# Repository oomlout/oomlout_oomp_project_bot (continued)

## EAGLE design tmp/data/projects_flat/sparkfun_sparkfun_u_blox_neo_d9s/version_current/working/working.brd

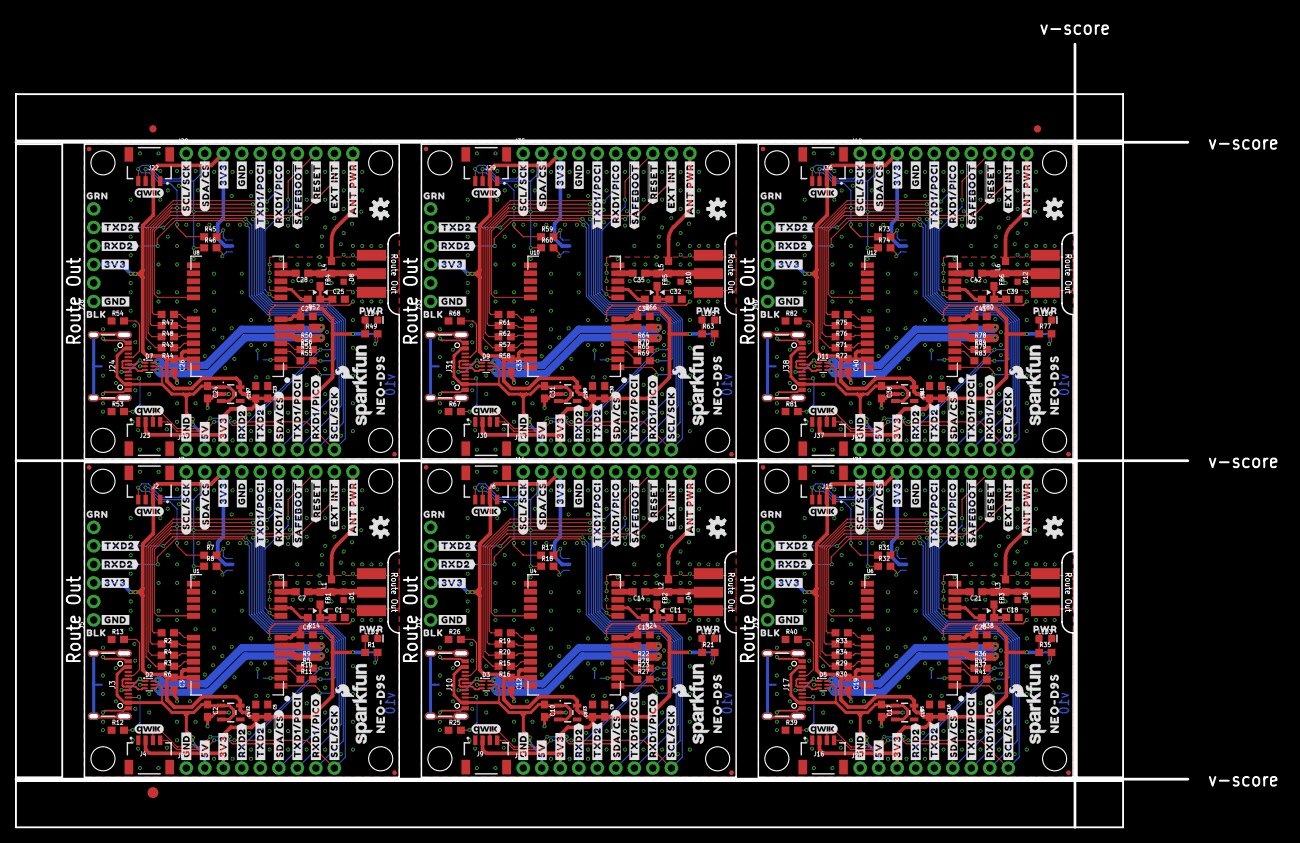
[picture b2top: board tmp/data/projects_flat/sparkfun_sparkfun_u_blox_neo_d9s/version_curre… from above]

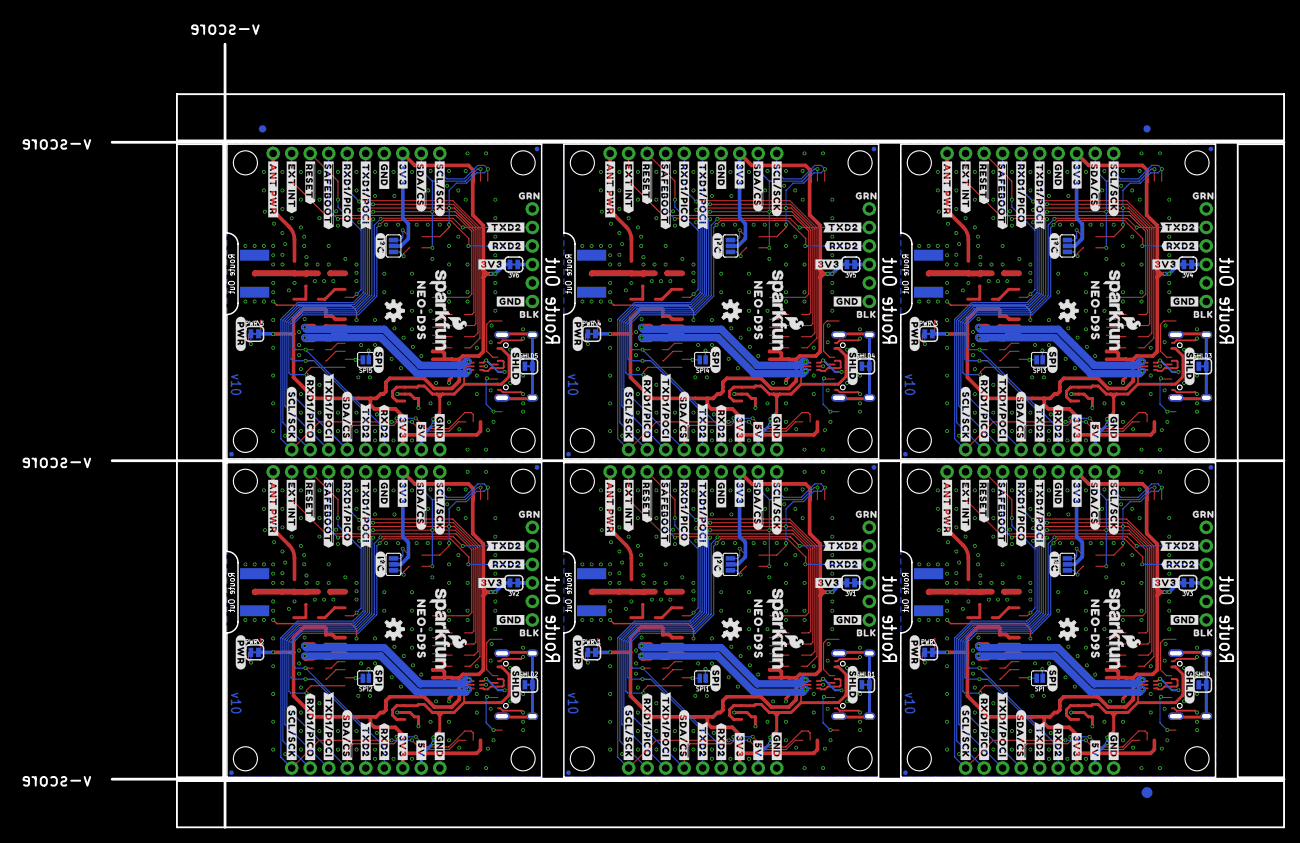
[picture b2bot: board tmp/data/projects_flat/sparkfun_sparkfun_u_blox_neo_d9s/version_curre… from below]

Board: 2 copper layers, 160.8 x 107.4 mm, 672 parts (237 on the bottom side), 228 nets.

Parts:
3V1, 3V2, 3V3, 3V4, 3V5, 3V6: JUMPER-SMT_2_NC_TRACE_SILK; SMT-JUMPER_2_NC_TRACE_SILK
C1, C7, C11, C14, C18, C21, C25, C28, C32, C35, C39, C42: 47pF; 0603
C2, C3, C4, C6, C8, C10, C12, C13, C15, C17, C19, C20, C22, C24, C26, C27, C29, C31, C33, C34, C36, C38, C40, C41: 1.0uF; 0603
C5, C9, C16, C23, C30, C37: 0.1uF; 0603
D1, D4, D6, D8, D10, D12: PESD0402-0402; 0402
D2, D3, D5, D7, D9, D11: PRTR5V0U2F; SOT886
E$1, E$2, E$3, E$4: FIDUCIAL-1X2
E$5, E$6: FIDUCIAL-1.5X3
FB1, FB2, FB3, FB4, FB5, FB6: 30Ω/1.8A; 0603
I2C, I2C1, I2C2, I2C3, I2C4, I2C5: JUMPER-SMT_3_NO_SILK; SMT-JUMPER_3_NO_SILK
J1, J11, J18, J25, J32, J39: ANTENNA-SMA-GROUNDEDEDGE_SMA; SMA-EDGE
J2, J4, J6, J9, J15, J16, J22, J23, J29, J30, J36, J37: Qwiic Right Angle; JST04_1MM_RA
J3, J10, J17, J24, J31, J38: USB-C-16P-2LAYER-PADS
J5, J12, J19, J26, J33, J40: 1X06_NO_SILK
J7, J14, J21, J28, J35, J42: 1X10_NO_SILK
J8, J13, J20, J27, J34, J41: 1X09_NO_SILK
JP1, JP2, JP7, JP8, JP9, JP10, JP15, JP16, JP17, JP18, JP24, JP25, JP26, JP27, JP31, JP33, JP34, JP35, JP36, JP41, JP42, JP43, JP91, JP101: STAND-OFF
JP3, JP4, JP5, JP6, JP11, JP12, JP13, JP14, JP19, JP20, JP21, JP22, JP23, JP28, JP29, JP30, JP32, JP37, JP38, JP39, JP40, JP61, JP71, JP81: FIDUCIALUFIDUCIAL; MICRO-FIDUCIAL
L1, L2, L3, L4, L5, L6: DNP; 0603_NO-CREAM
LED1, LED2, LED3, LED4, LED5, LED6: RED; LED-0603
LOGO1, LOGO4, LOGO5, LOGO8, LOGO9, LOGO12, LOGO13, LOGO16, LOGO17, LOGO20, LOGO21, LOGO24: OSHW-LOGOS; OSHW-LOGO-S
LOGO2, LOGO3, LOGO6, LOGO7, LOGO10, LOGO11, LOGO14, LOGO15, LOGO18, LOGO19, LOGO22, LOGO23: SFE_LOGO_NAME_FLAME.1_INCH; SFE_LOGO_NAME_FLAME_.1
PWR\, PWR\1, PWR\2, PWR\3, PWR\4, PWR\5: JUMPER-SMT_2_NC_TRACE_SILK; SMT-JUMPER_2_NC_TRACE_SILK
R1, R21, R35, R49, R63, R77: 1k; 0603
R2, R3, R4, R5, R6, R11, R15, R16, R19, R20, R27, R28, R29, R30, R33, R34, R41, R42, R43, R44, R47, R48, R55, R56, R57, R58, R61, R62, R69, R70, R71, R72, R75, R76, R83, R84: 33; 0603
R7, R8, R17, R18, R31, R32, R45, R46, R59, R60, R73, R74: 2.2k; 0603
R9, R10, R22, R23, R36, R37, R50, R51, R64, R65, R78, R79: 27; 0603
R12, R13, R25, R26, R39, R40, R53, R54, R67, R68, R81, R82: 5.1k; 0603
R14, R24, R38, R52, R66, R80: 10; 0603
SHLD, SHLD1, SHLD2, SHLD3, SHLD4, SHLD5: JUMPER-SMT_2_NC_TRACE_SILK; SMT-JUMPER_2_NC_TRACE_SILK
SPI, SPI1, SPI2, SPI3, SPI4, SPI5: JUMPER-SMT_2_NO_SILK; SMT-JUMPER_2_NO_SILK
U1, U4, U6, U8, U10, U12: U-BLOX_NEO-D9S-00B; NEO-M9N/M8T/M8U/D9S
U2, U3, U5, U7, U9, U11: 3.3V; SOT23-5
U$1, U$2, U$3, U$61, U$62, U$63, U$120, U$121, U$122, U$179, U$180, U$181, U$238, U$239, U$240, U$297, U$298, U$299: #GND#0
U$4, U$5, U$6, U$64, U$65, U$66, U$123, U$124, U$125, U$182, U$183, U$184, U$241, U$242, U$243, U$300, U$301, U$302: #GND#1
U$7, U$8, U$67, U$68, U$126, U$127, U$185, U$186, U$244, U$245, U$303, U$304: #TXD2#0
U$9, U$10, U$69, U$70, U$128, U$129, U$187, U$188, U$246, U$247, U$305, U$306: #TXD2#3
U$11, U$12, U$71, U$72, U$130, U$131, U$189, U$190, U$248, U$249, U$307, U$308: #RXD2#0
U$13, U$15, U$73, U$74, U$132, U$133, U$191, U$192, U$250, U$251, U$309, U$310: #RXD2#3
U$14, U$38, U$60, U$114, U$119, U$173, U$178, U$232, U$237, U$291, U$296, U$350: QWIIC_4MM
U$16, U$17, U$75, U$76, U$134, U$135, U$193, U$194, U$252, U$253, U$311, U$312: BLK0
U$18, U$19, U$77, U$78, U$136, U$137, U$195, U$196, U$254, U$255, U$313, U$314: GRN0
U$20, U$79, U$138, U$197, U$256, U$315: #5V#0
U$21, U$80, U$139, U$198, U$257, U$316: #5V#6
U$22, U$23, U$56, U$57, U$81, U$82, U$115, U$116, U$140, U$141, U$174, U$175, U$199, U$200, U$233, U$234, U$258, U$259, U$292, U$293, U$317, U$318, U$351, U$352: #3V3#0
U$24, U$25, U$83, U$84, U$142, U$143, U$201, U$202, U$260, U$261, U$319, U$320: #3V3#4
U$26, U$27, U$85, U$86, U$144, U$145, U$203, U$204, U$262, U$263, U$321, U$322: #SDA##CS##0
U$28, U$29, U$87, U$88, U$146, U$147, U$205, U$206, U$264, U$265, U$323, U$324: #SDA##CS##1
U$30, U$31, U$106, U$107, U$165, U$166, U$224, U$225, U$283, U$284, U$342, U$343: #TXD1#POCI#0
U$32, U$33, U$108, U$109, U$167, U$168, U$226, U$227, U$285, U$286, U$344, U$345: #TXD1#POCI#2
U$34, U$35, U$110, U$111, U$169, U$170, U$228, U$229, U$287, U$288, U$346, U$347: #RXD1#PICO#0
U$36, U$37, U$112, U$113, U$171, U$172, U$230, U$231, U$289, U$290, U$348, U$349: #RXD1#PICO#2
U$39, U$40, U$89, U$90, U$148, U$149, U$207, U$208, U$266, U$267, U$325, U$326: #SCL#SCK#0
U$41, U$42, U$91, U$92, U$150, U$151, U$209, U$210, U$268, U$269, U$327, U$328: #SCL#SCK#1
U$43, U$93, U$152, U$211, U$270, U$329: ##SAFEBOOT##0
U$44, U$94, U$153, U$212, U$271, U$330: ##SAFEBOOT##1
U$45, U$95, U$154, U$213, U$272, U$331: ##RESET##0
U$46, U$96, U$155, U$214, U$273, U$332: ##RESET##1
U$47, U$97, U$156, U$215, U$274, U$333: #EXT_INT#0
U$48, U$98, U$157, U$216, U$275, U$334: #EXT_INT#1
U$49, U$99, U$158, U$217, U$276, U$335: PWR0
U$50, U$100, U$159, U$218, U$277, U$336: #PWR#0
U$51, U$101, U$160, U$219, U$278, U$337: #SPI#0
U$52, U$102, U$161, U$220, U$279, U$338: #I�C#0
U$53, U$103, U$162, U$221, U$280, U$339: #SHLD#0
U$54, U$55, U$104, U$105, U$163, U$164, U$222, U$223, U$281, U$282, U$340, U$341: NEO#D9S0
U$58, U$117, U$176, U$235, U$294, U$353: #ANT_PWR#0
U$59, U$118, U$177, U$236, U$295, U$354: #ANT_PWR#1

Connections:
3.3V: 3V3.2, C3.1, C4.1, C5.2, C6.1, I2C.2, J2.2, J4.2, J7.3, J8.3, PWR\.2, U1.7, U1.22, U1.23, U2.5
3.3V1: 3V1.2, C8.1, C9.2, C12.1, C13.1, I2C1.2, J6.2, J9.2, J13.3, J14.3, PWR\1.2, U3.5, U4.7, U4.22, U4.23
3.3V2: 3V2.2, C15.1, C16.2, C19.1, C20.1, I2C2.2, J15.2, J16.2, J20.3, J21.3, PWR\2.2, U5.5, U6.7, U6.22, U6.23
3.3V3: 3V4.2, C22.1, C23.2, C26.1, C27.1, I2C3.2, J22.2, J23.2, J27.3, J28.3, PWR\3.2, U7.5, U8.7, U8.22, U8.23
3.3V4: 3V5.2, C29.1, C30.2, C33.1, C34.1, I2C4.2, J29.2, J30.2, J34.3, J35.3, PWR\4.2, U9.5, U10.7, U10.22, U10.23
3.3V5: 3V6.2, C36.1, C37.2, C40.1, C41.1, I2C5.2, J36.2, J37.2, J41.3, J42.3, PWR\5.2, U11.5, U12.7, U12.22, U12.23
5V: C2.1, D2.5, J3.VBUS1, J3.VBUS2, J8.2, U2.1, U2.3
5V1: C10.1, D3.5, J10.VBUS1, J10.VBUS2, J13.2, U3.1, U3.3
5V2: C17.1, D5.5, J17.VBUS1, J17.VBUS2, J20.2, U5.1, U5.3
5V3: C24.1, D7.5, J24.VBUS1, J24.VBUS2, J27.2, U7.1, U7.3
5V4: C31.1, D9.5, J31.VBUS1, J31.VBUS2, J34.2, U9.1, U9.3
5V5: C38.1, D11.5, J38.VBUS1, J38.VBUS2, J41.2, U11.1, U11.3
!RESET!: J7.8, U1.8
!RESET!1: J14.8, U4.8
!RESET!2: J21.8, U6.8
!RESET!3: J28.8, U8.8
!RESET!4: J35.8, U10.8
!RESET!5: J42.8, U12.8
!SAFEBOOT!: J7.7, U1.1
!SAFEBOOT!1: J14.7, U4.1
!SAFEBOOT!2: J21.7, U6.1
!SAFEBOOT!3: J28.7, U8.1
!SAFEBOOT!4: J35.7, U10.1
!SAFEBOOT!5: J42.7, U12.1
ANT: C7.2, U1.11
ANT1: C14.2, U4.11
ANT2: C21.2, U6.11
ANT3: C28.2, U8.11
ANT4: C35.2, U10.11
ANT5: C42.2, U12.11
ANT_PWR: J7.10, L1.2
ANT_PWR1: J14.10, L2.2
ANT_PWR2: J21.10, L3.2
ANT_PWR3: J28.10, L4.2
ANT_PWR4: J35.10, L5.2
ANT_PWR5: J42.10, L6.2
ANT_VCC: C1.1, FB1.2, R14.1
ANT_VCC1: C11.1, FB2.2, R24.1
ANT_VCC2: C18.1, FB3.2, R38.1
ANT_VCC3: C25.1, FB4.2, R52.1
ANT_VCC4: C32.1, FB5.2, R66.1
ANT_VCC5: C39.1, FB6.2, R80.1
D+: D2.6, R9.1
D+1: D3.6, R22.1
D+2: D5.6, R36.1
D+3: D7.6, R50.1
D+4: D9.6, R64.1
D+5: D11.6, R78.1
D-: D2.4, R10.1
D-1: D3.4, R23.1
D-2: D5.4, R37.1
D-3: D7.4, R51.1
D-4: D9.4, R65.1
D-5: D11.4, R79.1
D_SEL: SPI.2, U1.2
D_SEL1: SPI1.2, U4.2
D_SEL2: SPI2.2, U6.2
D_SEL3: SPI3.2, U8.2
D_SEL4: SPI4.2, U10.2
D_SEL5: SPI5.2, U12.2
EXT_INT: J7.9, U1.17
EXT_INT1: J14.9, U4.17
EXT_INT2: J21.9, U6.17
EXT_INT3: J28.9, U8.17
EXT_INT4: J35.9, U10.17
EXT_INT5: J42.9, U12.17
GND: C1.2, C2.2, C3.2, C4.2, C5.1, C6.2, D1.2, D2.2, J1.GND@0, J1.GND@1, J1.GND@2, J1.GND@3, J2.1, J3.GND, J3.GND2, J4.1, J5.1, J7.4, J8.1, LED1.C, R12.1, R13.1, SHLD.1, SPI.1, U1.10, U1.12, U1.13, U1.24, U2.2
GND1: C8.2, C9.1, C10.2, C11.2, C12.2, C13.2, D3.2, D4.2, J6.1, J9.1, J10.GND, J10.GND2, J11.GND@0, J11.GND@1, J11.GND@2, J11.GND@3, J12.1, J13.1, J14.4, LED2.C, R25.1, R26.1, SHLD1.1, SPI1.1, U3.2, U4.10, U4.12, U4.13, U4.24
GND2: C15.2, C16.1, C17.2, C18.2, C19.2, C20.2, D5.2, D6.2, J15.1, J16.1, J17.GND, J17.GND2, J18.GND@0, J18.GND@1, J18.GND@2, J18.GND@3, J19.1, J20.1, J21.4, LED3.C, R39.1, R40.1, SHLD2.1, SPI2.1, U5.2, U6.10, U6.12, U6.13, U6.24
GND3: C22.2, C23.1, C24.2, C25.2, C26.2, C27.2, D7.2, D8.2, J22.1, J23.1, J24.GND, J24.GND2, J25.GND@0, J25.GND@1, J25.GND@2, J25.GND@3, J26.1, J27.1, J28.4, LED4.C, R53.1, R54.1, SHLD3.1, SPI3.1, U7.2, U8.10, U8.12, U8.13, U8.24
GND4: C29.2, C30.1, C31.2, C32.2, C33.2, C34.2, D9.2, D10.2, J29.1, J30.1, J31.GND, J31.GND2, J32.GND@0, J32.GND@1, J32.GND@2, J32.GND@3, J33.1, J34.1, J35.4, LED5.C, R67.1, R68.1, SHLD4.1, SPI4.1, U9.2, U10.10, U10.12, U10.13, U10.24
GND5: C36.2, C37.1, C38.2, C39.2, C40.2, C41.2, D11.2, D12.2, J36.1, J37.1, J38.GND, J38.GND2, J39.GND@0, J39.GND@1, J39.GND@2, J39.GND@3, J40.1, J41.1, J42.4, LED6.C, R81.1, R82.1, SHLD5.1, SPI5.1, U11.2, U12.10, U12.12, U12.13, U12.24
unnamed: PWR\.1, R1.2
unnamed: R3.1, U1.20
unnamed: R2.1, U1.18
unnamed: R4.1, U1.19
unnamed: I2C.1, R8.2
unnamed: R6.1, U1.21
unnamed: J3.B5, R12.2
unnamed: I2C.3, R7.2
unnamed: J3.A5, R13.2
unnamed: LED1.A, R1.1
unnamed: R9.2, U1.6
unnamed: R10.2, U1.5
unnamed: 3V3.1, J5.3
unnamed: R11.1, U1.3
unnamed: R5.1, U1.4
unnamed: I2C1.1, R18.2
unnamed: I2C1.3, R17.2
unnamed: LED2.A, R21.1
unnamed: R22.2, U4.6
unnamed: R23.2, U4.5
unnamed: PWR\1.1, R21.2
unnamed: J10.B5, R25.2
unnamed: J10.A5, R26.2
unnamed: R27.1, U4.3
unnamed: R28.1, U4.4
unnamed: R15.1, U4.20
unnamed: R16.1, U4.21
unnamed: R19.1, U4.18
unnamed: R20.1, U4.19
unnamed: 3V1.1, J12.3
unnamed: I2C2.1, R32.2
unnamed: I2C2.3, R31.2
unnamed: LED3.A, R35.1
unnamed: R36.2, U6.6
unnamed: R37.2, U6.5
unnamed: PWR\2.1, R35.2
unnamed: J17.B5, R39.2
unnamed: J17.A5, R40.2
unnamed: R41.1, U6.3
unnamed: R42.1, U6.4
unnamed: R29.1, U6.20
unnamed: R30.1, U6.21
unnamed: R33.1, U6.18
unnamed: R34.1, U6.19
unnamed: 3V2.1, J19.3
unnamed: I2C3.1, R46.2
unnamed: I2C3.3, R45.2
unnamed: LED4.A, R49.1
unnamed: R50.2, U8.6
unnamed: R51.2, U8.5
unnamed: PWR\3.1, R49.2
unnamed: J24.B5, R53.2
unnamed: J24.A5, R54.2
unnamed: R55.1, U8.3
unnamed: R56.1, U8.4
unnamed: R43.1, U8.20
unnamed: R44.1, U8.21
unnamed: R47.1, U8.18
unnamed: R48.1, U8.19
unnamed: 3V4.1, J26.3
unnamed: I2C4.1, R60.2
unnamed: I2C4.3, R59.2
unnamed: LED5.A, R63.1
unnamed: R64.2, U10.6
unnamed: R65.2, U10.5
unnamed: PWR\4.1, R63.2
unnamed: J31.B5, R67.2
unnamed: J31.A5, R68.2
unnamed: R69.1, U10.3
unnamed: R70.1, U10.4
unnamed: R57.1, U10.20
unnamed: R58.1, U10.21
unnamed: R61.1, U10.18
unnamed: R62.1, U10.19
unnamed: 3V5.1, J33.3
unnamed: I2C5.1, R74.2
unnamed: I2C5.3, R73.2
unnamed: LED6.A, R77.1
unnamed: R78.2, U12.6
unnamed: R79.2, U12.5
unnamed: PWR\5.1, R77.2
unnamed: J38.B5, R81.2
unnamed: J38.A5, R82.2
unnamed: R83.1, U12.3
unnamed: R84.1, U12.4
unnamed: R71.1, U12.20
unnamed: R72.1, U12.21
unnamed: R75.1, U12.18
unnamed: R76.1, U12.19
unnamed: 3V6.1, J40.3
RXD1: J12.4, J13.4, R28.2
RXD1/PICO: J7.6, J8.8, R6.2
RXD1/PICO1: J13.8, J14.6, R16.2
RXD1/PICO2: J20.8, J21.6, R30.2
RXD1/PICO3: J27.8, J28.6, R44.2
RXD1/PICO4: J34.8, J35.6, R58.2
RXD1/PICO5: J41.8, J42.6, R72.2
RXD2: J5.4, J8.4, R5.2
RXD3: J19.4, J20.4, R42.2
RXD4: J26.4, J27.4, R56.2
RXD5: J33.4, J34.4, R70.2
RXD6: J40.4, J41.4, R84.2
SCL/SCK: J2.4, J4.4, J7.1, J8.9, R4.2, R7.1
SCL/SCK1: J6.4, J9.4, J13.9, J14.1, R17.1, R20.2
SCL/SCK2: J15.4, J16.4, J20.9, J21.1, R31.1, R34.2
SCL/SCK3: J22.4, J23.4, J27.9, J28.1, R45.1, R48.2
SCL/SCK4: J29.4, J30.4, J34.9, J35.1, R59.1, R62.2
SCL/SCK5: J36.4, J37.4, J41.9, J42.1, R73.1, R76.2
SDA/!CS!: J2.3, J4.3, J7.2, J8.6, R2.2, R8.1
SDA/!CS!1: J6.3, J9.3, J13.6, J14.2, R18.1, R19.2
SDA/!CS!2: J15.3, J16.3, J20.6, J21.2, R32.1, R33.2
SDA/!CS!3: J22.3, J23.3, J27.6, J28.2, R46.1, R47.2
SDA/!CS!4: J29.3, J30.3, J34.6, J35.2, R60.1, R61.2
SDA/!CS!5: J36.3, J37.3, J41.6, J42.2, R74.1, R75.2
SHIELD: J3.SHLD1, J3.SHLD2, J3.SHLD3, J3.SHLD4, SHLD.2
SHIELD1: J10.SHLD1, J10.SHLD2, J10.SHLD3, J10.SHLD4, SHLD1.2
SHIELD2: J17.SHLD1, J17.SHLD2, J17.SHLD3, J17.SHLD4, SHLD2.2
SHIELD3: J24.SHLD1, J24.SHLD2, J24.SHLD3, J24.SHLD4, SHLD3.2
SHIELD4: J31.SHLD1, J31.SHLD2, J31.SHLD3, J31.SHLD4, SHLD4.2
SHIELD5: J38.SHLD1, J38.SHLD2, J38.SHLD3, J38.SHLD4, SHLD5.2
SMA: C7.1, D1.1, FB1.1, J1.SIG, L1.1
SMA1: C14.1, D4.1, FB2.1, J11.SIG, L2.1
SMA2: C21.1, D6.1, FB3.1, J18.SIG, L3.1
SMA3: C28.1, D8.1, FB4.1, J25.SIG, L4.1
SMA4: C35.1, D10.1, FB5.1, J32.SIG, L5.1
SMA5: C42.1, D12.1, FB6.1, J39.SIG, L6.1
TXD1: J12.5, J13.5, R27.2
TXD1/POCI: J7.5, J8.7, R3.2
TXD1/POCI1: J13.7, J14.5, R15.2
TXD1/POCI2: J20.7, J21.5, R29.2
TXD1/POCI3: J27.7, J28.5, R43.2
TXD1/POCI4: J34.7, J35.5, R57.2
TXD1/POCI5: J41.7, J42.5, R71.2
TXD2: J5.5, J8.5, R11.2
TXD3: J19.5, J20.5, R41.2
TXD4: J26.5, J27.5, R55.2
TXD5: J33.5, J34.5, R69.2
TXD6: J40.5, J41.5, R83.2
USB_D+: D2.1, J3.A6, J3.B6
USB_D+1: D3.1, J10.A6, J10.B6
USB_D+2: D5.1, J17.A6, J17.B6
USB_D+3: D7.1, J24.A6, J24.B6
USB_D+4: D9.1, J31.A6, J31.B6
USB_D+5: D11.1, J38.A6, J38.B6
USB_D-: D2.3, J3.A7, J3.B7
USB_D-1: D3.3, J10.A7, J10.B7
USB_D-2: D5.3, J17.A7, J17.B7
USB_D-3: D7.3, J24.A7, J24.B7
USB_D-4: D9.3, J31.A7, J31.B7
USB_D-5: D11.3, J38.A7, J38.B7
VCC_RF: R14.2, U1.9
VCC_RF1: R24.2, U4.9
VCC_RF2: R38.2, U6.9
VCC_RF3: R52.2, U8.9
VCC_RF4: R66.2, U10.9
VCC_RF5: R80.2, U12.9

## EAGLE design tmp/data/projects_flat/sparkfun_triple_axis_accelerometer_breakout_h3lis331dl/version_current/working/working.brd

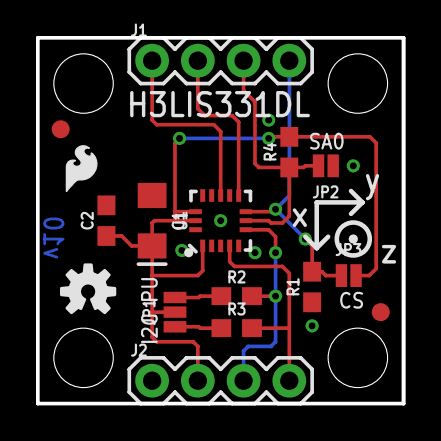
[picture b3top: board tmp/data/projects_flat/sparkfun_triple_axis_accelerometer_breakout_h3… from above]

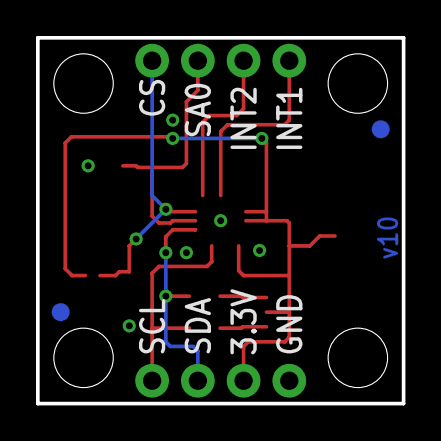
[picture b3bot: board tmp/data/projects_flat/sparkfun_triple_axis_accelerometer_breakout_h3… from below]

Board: 2 copper layers, 20.3 x 20.3 mm, 23 parts (2 on the bottom side), 10 nets.

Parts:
C1: 10uF; EIA3216
C2: 0.1uF; 0603
FRAME1: FRAME-LETTER; CREATIVE_COMMONS
J1, J2: 1X04
JP1: JUMPER-SMT_3_2-NC_PASTE_NO-SILK; SMT-JUMPER_3_2-NC_PASTE_NO-SILK
JP2: JUMPER-SMT_2_NO_NO-SILK; SMT-JUMPER_2_NO_NO-SILK
JP3: JUMPER-SMT_2_NC_PASTE_NO-SILK; SMT-JUMPER_2_NC_PASTE_NO-SILK
JP4, JP5, JP6, JP7: FIDUCIAL1X2; FIDUCIAL-1X2
JP8, JP9, JP10, JP11: STAND-OFF
LOGO1: SFE_LOGO_FLAME.1_INCH; SFE_LOGO_FLAME_.1
LOGO2: OSHW-LOGOS; OSHW-LOGO-S
R1, R4: 10k; 0603
R2, R3: 4.7k; 0603
U1: H3LIS331DL; LGA-16-3X3

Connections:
3.3V: C1.+, C2.1, J2.2, JP1.2, JP3.2, R4.2, U1.1, U1.14, U1.15
CS: J1.4, JP3.1, R1.2, U1.8
GND: C1.-, C2.2, J2.1, JP2.1, R1.1, U1.5, U1.10, U1.12, U1.13, U1.16
INT1: J1.1, U1.11
INT2: J1.2, U1.9
unnamed: JP1.1, R3.1
unnamed: JP1.3, R2.1
SA0: J1.3, JP2.2, R4.1, U1.7
SCL: J2.4, R3.2, U1.4
SDA: J2.3, R2.2, U1.6

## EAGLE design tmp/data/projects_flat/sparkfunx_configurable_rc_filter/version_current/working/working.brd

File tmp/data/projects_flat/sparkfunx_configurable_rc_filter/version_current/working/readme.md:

# Configurable_RC_Filter by sparkfunX  
This is a harvested standardized copy of a project from github.  
The original project can be found at:  
https://github.com/sparkfunX/Configurable_RC_Filter  
Please consult that link for additional, details, files, and license information.  
Note: It was auto harvested and if the original repo had more than one board file or anything out of the ordinary the files here are likely not representative.

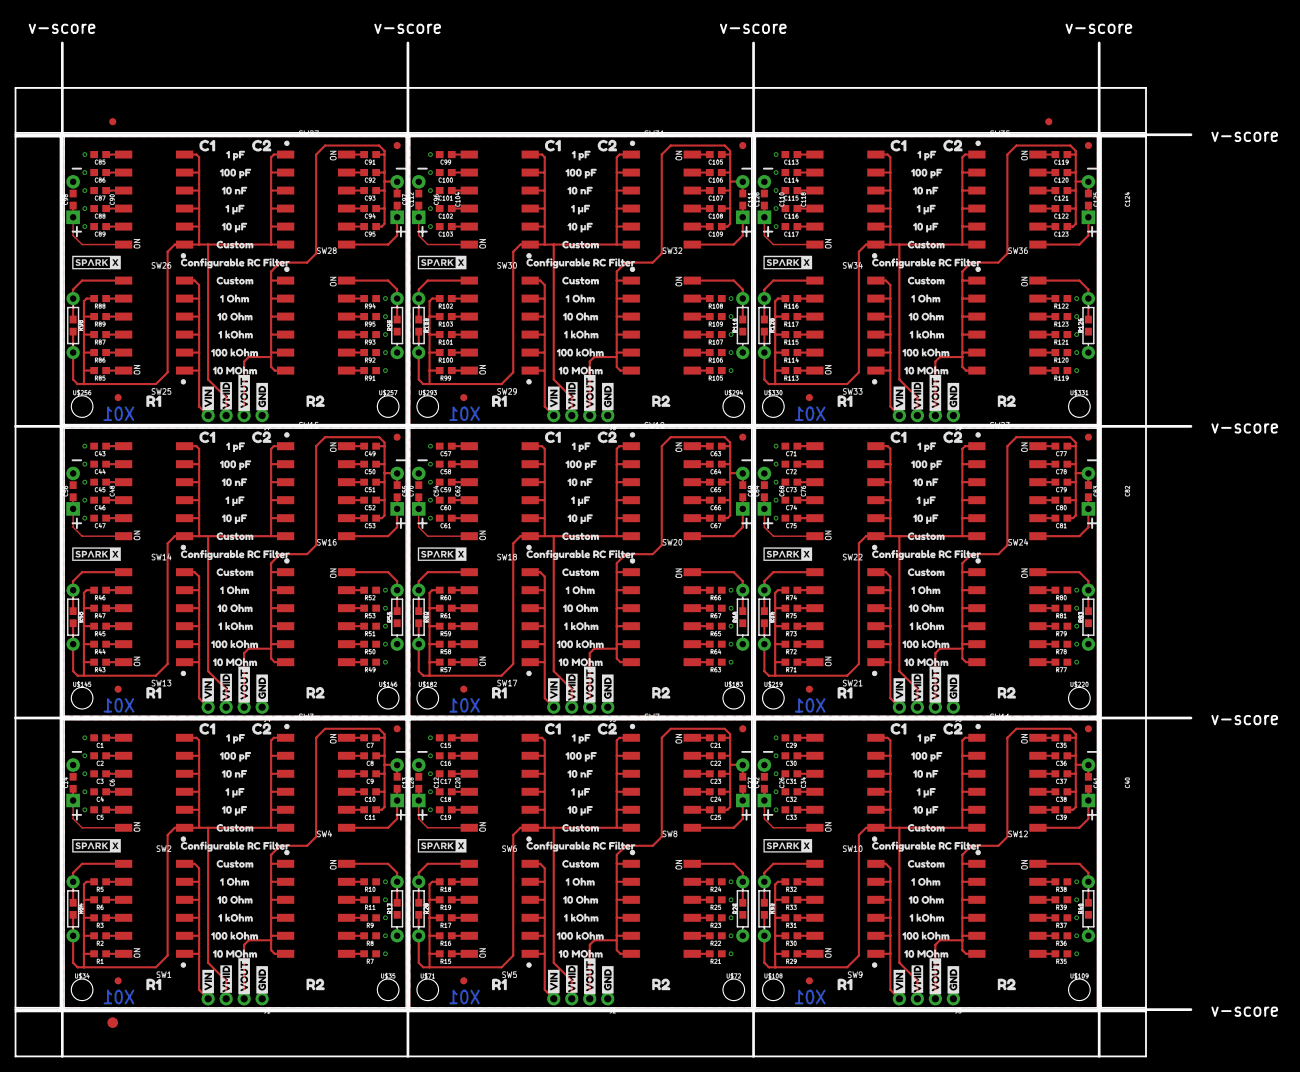
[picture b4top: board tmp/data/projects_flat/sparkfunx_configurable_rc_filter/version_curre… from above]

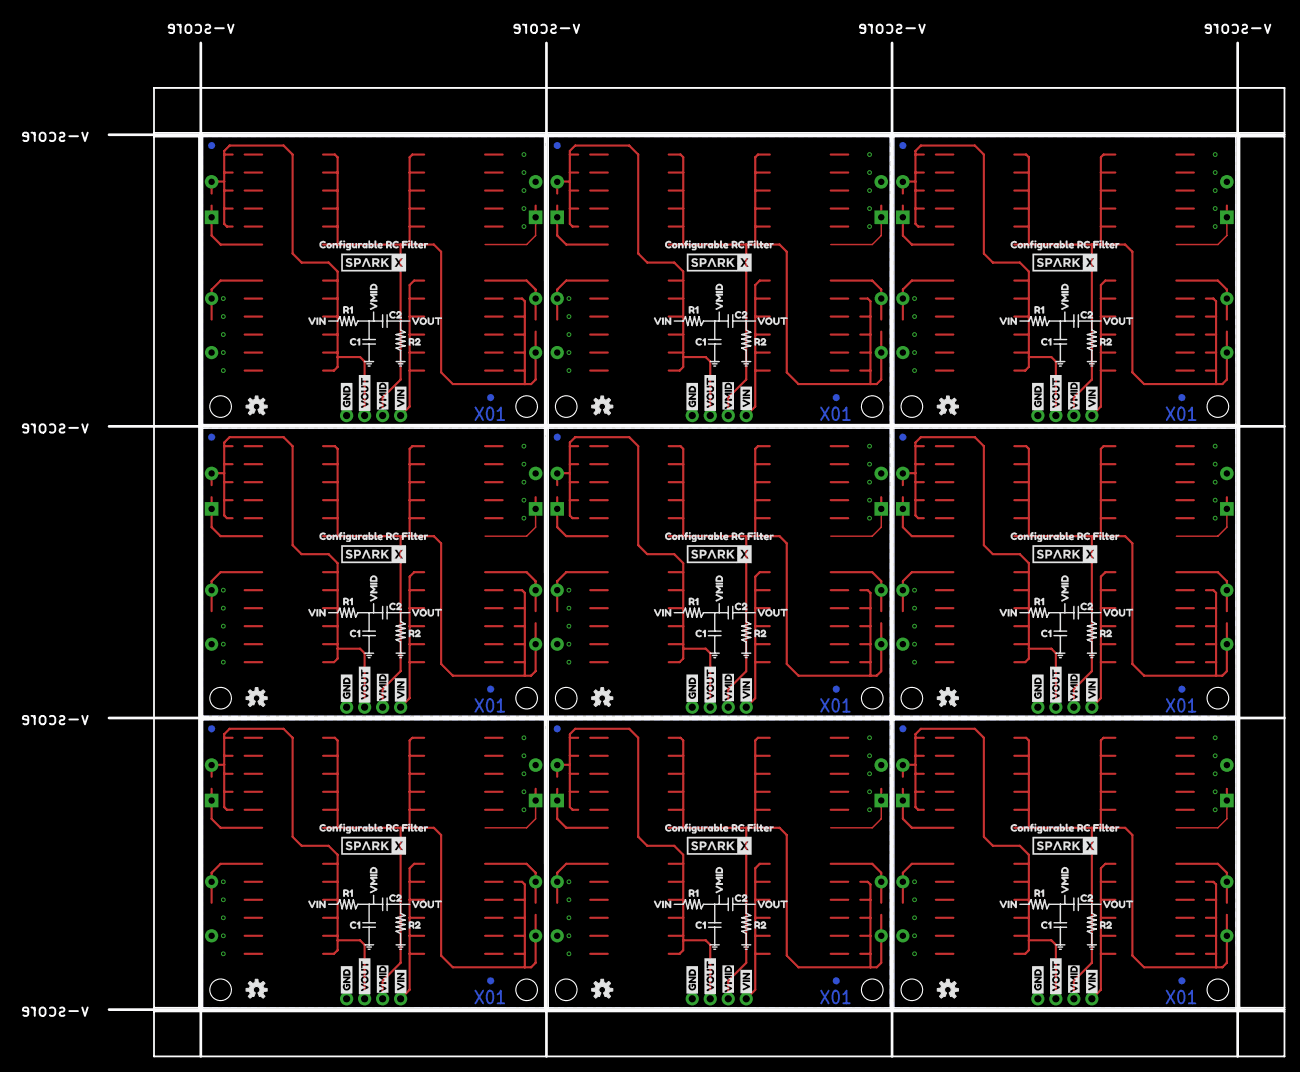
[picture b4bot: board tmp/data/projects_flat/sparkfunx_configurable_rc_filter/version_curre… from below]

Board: 2 copper layers, 165.9 x 143.0 mm, 678 parts (144 on the bottom side), 252 nets.

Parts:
C1, C7, C15, C21, C29, C35, C43, C49, C57, C63, C71, C77, C85, C91, C99, C105, C113, C119: 1.0pF; 0603
C2, C8, C16, C22, C30, C36, C44, C50, C58, C64, C72, C78, C86, C92, C100, C106, C114, C120: 100pF; 0603
C3, C9, C17, C23, C31, C37, C45, C51, C59, C65, C73, C79, C87, C93, C101, C107, C115, C121: 10nF; 0603
C4, C10, C18, C24, C32, C38, C46, C52, C60, C66, C74, C80, C88, C94, C102, C108, C116, C122: 1.0uF; 0603
C5, C11, C19, C25, C33, C39, C47, C53, C61, C67, C75, C81, C89, C95, C103, C109, C117, C123: 10uF; 0603
C6, C12, C20, C26, C34, C40, C48, C54, C62, C68, C76, C82, C90, C96, C104, C110, C118, C124: 1000UF-RADIAL-5MM-25V-20%-NO-SILK; CPOL-RADIAL-5MM-10MM-NS
C13, C14, C27, C28, C41, C42, C55, C56, C69, C70, C83, C84, C97, C98, C111, C112, C125, C126: 0603
E$1, E$2: FIDUCIAL-1X2
E$3: FIDUCIAL-1.5X3
FD1, FD2, FD3, FD4, FD5, FD6, FD7, FD8, FD9, FD10, FD11, FD12, FD13, FD14, FD15, FD16, FD17, FD18, FD19, FD20, FD21, FD22, FD23, FD24, FD25, FD26, FD27, FD28, FD29, FD30, FD31, FD32, FD33, FD34, FD35, FD36: FIDUCIAL1X2; FIDUCIAL-1X2
J1, J2, J3, J4, J5, J6, J7, J8, J9: 1X04_NO_SILK
LOGO1, LOGO2, LOGO3, LOGO4, LOGO5, LOGO6, LOGO7, LOGO8, LOGO9: OSHW-LOGOS; OSHW-LOGO-S
R1, R7, R15, R21, R29, R35, R43, R49, R57, R63, R71, R77, R85, R91, R99, R105, R113, R119: 10M; 0603
R2, R8, R16, R22, R30, R36, R44, R50, R58, R64, R72, R78, R86, R92, R100, R106, R114, R120: 100k; 0603
R3, R9, R17, R23, R31, R37, R45, R51, R59, R65, R73, R79, R87, R93, R101, R107, R115, R121: 1k; 0603
R4, R12, R20, R26, R34, R40, R48, R54, R62, R68, R76, R82, R90, R96, R104, R110, R118, R124: AXIAL-0.3
R5, R10, R18, R24, R32, R38, R46, R52, R60, R66, R74, R80, R88, R94, R102, R108, R116, R122: 1; 0603
R6, R11, R19, R25, R33, R39, R47, R53, R61, R67, R75, R81, R89, R95, R103, R109, R117, R123: 10; 0603
R13, R14, R27, R28, R41, R42, R55, R56, R69, R70, R83, R84, R97, R98, R111, R112, R125, R126: 0603
SW1, SW2, SW3, SW4, SW5, SW6, SW7, SW8, SW9, SW10, SW11, SW12, SW13, SW14, SW15, SW16, SW17, SW18, SW19, SW20, SW21, SW22, SW23, SW24, SW25, SW26, SW27, SW28, SW29, SW30, SW31, SW32, SW33, SW34, SW35, SW36: DIP-06; DIPSWITCH-06-SMD
U$1, U$38, U$75, U$112, U$149, U$186, U$223, U$260, U$297: 1_#F9
U$2, U$39, U$76, U$113, U$150, U$187, U$224, U$261, U$298: 1_KOHM7
U$3, U$40, U$77, U$114, U$151, U$188, U$225, U$262, U$299: 10_#F8
U$4, U$41, U$78, U$115, U$152, U$189, U$226, U$263, U$300: 10_MOHM6
U$5, U$6, U$42, U$43, U$79, U$80, U$116, U$117, U$153, U$154, U$190, U$191, U$227, U$228, U$264, U$265, U$301, U$302: GND0
U$7, U$8, U$44, U$45, U$81, U$82, U$118, U$119, U$155, U$156, U$192, U$193, U$229, U$230, U$266, U$267, U$303, U$304: VIN1
U$9, U$10, U$46, U$47, U$83, U$84, U$120, U$121, U$157, U$158, U$194, U$195, U$231, U$232, U$268, U$269, U$305, U$306: VMID3
U$11, U$12, U$48, U$49, U$85, U$86, U$122, U$123, U$159, U$160, U$196, U$197, U$233, U$234, U$270, U$271, U$307, U$308: VOUT3
U$13, U$50, U$87, U$124, U$161, U$198, U$235, U$272, U$309: 10_NF11
U$14, U$51, U$88, U$125, U$162, U$199, U$236, U$273, U$310: 10_OHM4
U$15, U$52, U$89, U$126, U$163, U$200, U$237, U$274, U$311: 100_KOHM10
U$16, U$53, U$90, U$127, U$164, U$201, U$238, U$275, U$312: C10
U$17, U$54, U$91, U$128, U$165, U$202, U$239, U$276, U$313: C21
U$18, U$27, U$55, U$64, U$92, U$101, U$129, U$138, U$166, U$175, U$203, U$212, U$240, U$249, U$277, U$286, U$314, U$323: R12
U$19, U$28, U$56, U$65, U$93, U$102, U$130, U$139, U$167, U$176, U$204, U$213, U$241, U$250, U$278, U$287, U$315, U$324: R23
U$20, U$57, U$94, U$131, U$168, U$205, U$242, U$279, U$316: _1_OHM5
U$21, U$58, U$95, U$132, U$169, U$206, U$243, U$280, U$317: _1_PF13
U$22, U$59, U$96, U$133, U$170, U$207, U$244, U$281, U$318: _100_PF12
U$23, U$24, U$60, U$61, U$97, U$98, U$134, U$135, U$171, U$172, U$208, U$209, U$245, U$246, U$282, U$283, U$319, U$320: CUSTOM3
U$25, U$62, U$99, U$136, U$173, U$210, U$247, U$284, U$321: C11
U$26, U$63, U$100, U$137, U$174, U$211, U$248, U$285, U$322: C20
U$29, U$66, U$103, U$140, U$177, U$214, U$251, U$288, U$325: VIN4
U$30, U$67, U$104, U$141, U$178, U$215, U$252, U$289, U$326: VMID5
U$31, U$68, U$105, U$142, U$179, U$216, U$253, U$290, U$327: VOUT6
U$32, U$33, U$69, U$70, U$106, U$107, U$143, U$144, U$180, U$181, U$217, U$218, U$254, U$255, U$291, U$292, U$328, U$329: CONFIGURABLE_RC_FILTER0
U$34, U$35, U$71, U$72, U$108, U$109, U$145, U$146, U$182, U$183, U$219, U$220, U$256, U$257, U$293, U$294, U$330, U$331: STAND-OFF-TIGHT
U$36, U$73, U$110, U$147, U$184, U$221, U$258, U$295, U$332: SPARKX-SMALL
U$37, U$74, U$111, U$148, U$185, U$222, U$259, U$296, U$333: SPARKX-MEDIUM

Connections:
GND: C1.2, C2.2, C3.2, C4.2, C5.2, C6.-, C14.2, J1.1, R7.1, R8.1, R9.1, R10.1, R11.1, R12.P$1, R13.1
GND1: C15.2, C16.2, C17.2, C18.2, C19.2, C20.-, C28.2, J2.1, R21.1, R22.1, R23.1, R24.1, R25.1, R26.P$1, R27.1
GND2: C29.2, C30.2, C31.2, C32.2, C33.2, C34.-, C42.2, J3.1, R35.1, R36.1, R37.1, R38.1, R39.1, R40.P$1, R41.1
GND3: C43.2, C44.2, C45.2, C46.2, C47.2, C48.-, C56.2, J4.1, R49.1, R50.1, R51.1, R52.1, R53.1, R54.P$1, R55.1
GND4: C57.2, C58.2, C59.2, C60.2, C61.2, C62.-, C70.2, J5.1, R63.1, R64.1, R65.1, R66.1, R67.1, R68.P$1, R69.1
GND5: C71.2, C72.2, C73.2, C74.2, C75.2, C76.-, C84.2, J6.1, R77.1, R78.1, R79.1, R80.1, R81.1, R82.P$1, R83.1
GND6: C85.2, C86.2, C87.2, C88.2, C89.2, C90.-, C98.2, J7.1, R91.1, R92.1, R93.1, R94.1, R95.1, R96.P$1, R97.1
GND7: C99.2, C100.2, C101.2, C102.2, C103.2, C104.-, C112.2, J8.1, R105.1, R106.1, R107.1, R108.1, R109.1, R110.P$1, R111.1
GND8: C113.2, C114.2, C115.2, C116.2, C117.2, C118.-, C126.2, J9.1, R119.1, R120.1, R121.1, R122.1, R123.1, R124.P$1, R125.1
unnamed: R1.1, SW1.12
unnamed: R2.1, SW1.11
unnamed: C1.1, SW2.7
unnamed: R3.1, SW1.10
unnamed: R6.1, SW1.9
unnamed: R5.1, SW1.8
unnamed: R4.P$1, R14.1, SW1.7
unnamed: C2.1, SW2.8
unnamed: C3.1, SW2.9
unnamed: C4.1, SW2.10
unnamed: C5.1, SW2.11
unnamed: C6.+, C14.1, SW2.12
unnamed: C12.+, C13.2, SW3.7
unnamed: C11.2, SW3.8
unnamed: C10.2, SW3.9
unnamed: C9.2, SW3.10
unnamed: C8.2, SW3.11
unnamed: C7.2, SW3.12
unnamed: R7.2, SW4.7
unnamed: R8.2, SW4.8
unnamed: R9.2, SW4.9
unnamed: R12.P$2, R13.2, SW4.12
unnamed: R10.2, SW4.11
unnamed: R11.2, SW4.10
unnamed: R15.1, SW5.12
unnamed: R16.1, SW5.11
unnamed: R17.1, SW5.10
unnamed: R19.1, SW5.9
unnamed: R18.1, SW5.8
unnamed: R20.P$1, R28.1, SW5.7
unnamed: C15.1, SW6.7
unnamed: C16.1, SW6.8
unnamed: C17.1, SW6.9
unnamed: C18.1, SW6.10
unnamed: C19.1, SW6.11
unnamed: C20.+, C28.1, SW6.12
unnamed: R21.2, SW8.7
unnamed: R22.2, SW8.8
unnamed: R23.2, SW8.9
unnamed: R26.P$2, R27.2, SW8.12
unnamed: R24.2, SW8.11
unnamed: R25.2, SW8.10
unnamed: C26.+, C27.2, SW7.7
unnamed: C25.2, SW7.8
unnamed: C24.2, SW7.9
unnamed: C23.2, SW7.10
unnamed: C22.2, SW7.11
unnamed: C21.2, SW7.12
unnamed: R29.1, SW9.12
unnamed: R30.1, SW9.11
unnamed: R31.1, SW9.10
unnamed: R33.1, SW9.9
unnamed: R32.1, SW9.8
unnamed: R34.P$1, R42.1, SW9.7
unnamed: C29.1, SW10.7
unnamed: C30.1, SW10.8
unnamed: C31.1, SW10.9
unnamed: C32.1, SW10.10
unnamed: C33.1, SW10.11
unnamed: C34.+, C42.1, SW10.12
unnamed: R35.2, SW12.7
unnamed: R36.2, SW12.8
unnamed: R37.2, SW12.9
unnamed: R40.P$2, R41.2, SW12.12
unnamed: R38.2, SW12.11
unnamed: R39.2, SW12.10
unnamed: C40.+, C41.2, SW11.7
unnamed: C39.2, SW11.8
unnamed: C38.2, SW11.9
unnamed: C37.2, SW11.10
unnamed: C36.2, SW11.11
unnamed: C35.2, SW11.12
unnamed: R43.1, SW13.12
unnamed: R44.1, SW13.11
unnamed: R45.1, SW13.10
unnamed: R47.1, SW13.9
unnamed: R46.1, SW13.8
unnamed: R48.P$1, R56.1, SW13.7
unnamed: C43.1, SW14.7
unnamed: C44.1, SW14.8
unnamed: C45.1, SW14.9
unnamed: C46.1, SW14.10
unnamed: C47.1, SW14.11
unnamed: C48.+, C56.1, SW14.12
unnamed: R49.2, SW16.7
unnamed: R50.2, SW16.8
unnamed: R51.2, SW16.9
unnamed: R54.P$2, R55.2, SW16.12
unnamed: R52.2, SW16.11
unnamed: R53.2, SW16.10
unnamed: C54.+, C55.2, SW15.7
unnamed: C53.2, SW15.8
unnamed: C52.2, SW15.9
unnamed: C51.2, SW15.10
unnamed: C50.2, SW15.11
unnamed: C49.2, SW15.12
unnamed: R57.1, SW17.12
unnamed: R58.1, SW17.11
unnamed: R59.1, SW17.10
unnamed: R61.1, SW17.9
unnamed: R60.1, SW17.8
unnamed: R62.P$1, R70.1, SW17.7
unnamed: C57.1, SW18.7
unnamed: C58.1, SW18.8
unnamed: C59.1, SW18.9
unnamed: C60.1, SW18.10
unnamed: C61.1, SW18.11
unnamed: C62.+, C70.1, SW18.12
unnamed: R63.2, SW20.7
unnamed: R64.2, SW20.8
unnamed: R65.2, SW20.9
unnamed: R68.P$2, R69.2, SW20.12
unnamed: R66.2, SW20.11
unnamed: R67.2, SW20.10
unnamed: C68.+, C69.2, SW19.7
unnamed: C67.2, SW19.8
unnamed: C66.2, SW19.9
unnamed: C65.2, SW19.10
unnamed: C64.2, SW19.11
unnamed: C63.2, SW19.12
unnamed: R71.1, SW21.12
unnamed: R72.1, SW21.11
unnamed: R73.1, SW21.10
unnamed: R75.1, SW21.9
unnamed: R74.1, SW21.8
unnamed: R76.P$1, R84.1, SW21.7
unnamed: C71.1, SW22.7
unnamed: C72.1, SW22.8
unnamed: C73.1, SW22.9
unnamed: C74.1, SW22.10
unnamed: C75.1, SW22.11
unnamed: C76.+, C84.1, SW22.12
unnamed: R77.2, SW24.7
unnamed: R78.2, SW24.8
unnamed: R79.2, SW24.9
unnamed: R82.P$2, R83.2, SW24.12
unnamed: R80.2, SW24.11
unnamed: R81.2, SW24.10
unnamed: C82.+, C83.2, SW23.7
unnamed: C81.2, SW23.8
unnamed: C80.2, SW23.9
unnamed: C79.2, SW23.10
unnamed: C78.2, SW23.11
unnamed: C77.2, SW23.12
unnamed: R85.1, SW25.12
unnamed: R86.1, SW25.11
unnamed: R87.1, SW25.10
unnamed: R89.1, SW25.9
unnamed: R88.1, SW25.8
unnamed: R90.P$1, R98.1, SW25.7
unnamed: C85.1, SW26.7
unnamed: C86.1, SW26.8
unnamed: C87.1, SW26.9
unnamed: C88.1, SW26.10
unnamed: C89.1, SW26.11
unnamed: C90.+, C98.1, SW26.12
unnamed: R91.2, SW28.7
unnamed: R92.2, SW28.8
unnamed: R93.2, SW28.9
unnamed: R96.P$2, R97.2, SW28.12
unnamed: R94.2, SW28.11
unnamed: R95.2, SW28.10
unnamed: C96.+, C97.2, SW27.7
unnamed: C95.2, SW27.8
unnamed: C94.2, SW27.9
unnamed: C93.2, SW27.10
unnamed: C92.2, SW27.11
unnamed: C91.2, SW27.12
unnamed: R99.1, SW29.12
unnamed: R100.1, SW29.11
unnamed: R101.1, SW29.10
unnamed: R103.1, SW29.9
unnamed: R102.1, SW29.8
unnamed: R104.P$1, R112.1, SW29.7
unnamed: C99.1, SW30.7
unnamed: C100.1, SW30.8
unnamed: C101.1, SW30.9
unnamed: C102.1, SW30.10
unnamed: C103.1, SW30.11
unnamed: C104.+, C112.1, SW30.12
unnamed: R105.2, SW32.7
unnamed: R106.2, SW32.8
unnamed: R107.2, SW32.9
unnamed: R110.P$2, R111.2, SW32.12
unnamed: R108.2, SW32.11
unnamed: R109.2, SW32.10
unnamed: C110.+, C111.2, SW31.7
unnamed: C109.2, SW31.8
unnamed: C108.2, SW31.9
unnamed: C107.2, SW31.10
unnamed: C106.2, SW31.11
unnamed: C105.2, SW31.12
unnamed: R113.1, SW33.12
unnamed: R114.1, SW33.11
unnamed: R115.1, SW33.10
unnamed: R117.1, SW33.9
unnamed: R116.1, SW33.8
unnamed: R118.P$1, R126.1, SW33.7
unnamed: C113.1, SW34.7
unnamed: C114.1, SW34.8
unnamed: C115.1, SW34.9
unnamed: C116.1, SW34.10
unnamed: C117.1, SW34.11
unnamed: C118.+, C126.1, SW34.12
unnamed: R119.2, SW36.7
unnamed: R120.2, SW36.8
unnamed: R121.2, SW36.9
unnamed: R124.P$2, R125.2, SW36.12
unnamed: R122.2, SW36.11
unnamed: R123.2, SW36.10
unnamed: C124.+, C125.2, SW35.7
unnamed: C123.2, SW35.8
unnamed: C122.2, SW35.9
unnamed: C121.2, SW35.10
unnamed: C120.2, SW35.11
unnamed: C119.2, SW35.12
VDDA: J1.3, R1.2, R2.2, R3.2, R4.P$2, R5.2, R6.2, R14.2, SW2.1, SW2.2, SW2.3, SW2.4, SW2.5, SW2.6, SW3.1, SW3.2, SW3.3, SW3.4, SW3.5, SW3.6
VDDA1: J2.3, R15.2, R16.2, R17.2, R18.2, R19.2, R20.P$2, R28.2, SW6.1, SW6.2, SW6.3, SW6.4, SW6.5, SW6.6, SW7.1, SW7.2, SW7.3, SW7.4, SW7.5, SW7.6
VDDA2: J3.3, R29.2, R30.2, R31.2, R32.2, R33.2, R34.P$2, R42.2, SW10.1, SW10.2, SW10.3, SW10.4, SW10.5, SW10.6, SW11.1, SW11.2, SW11.3, SW11.4, SW11.5, SW11.6
VDDA3: J4.3, R43.2, R44.2, R45.2, R46.2, R47.2, R48.P$2, R56.2, SW14.1, SW14.2, SW14.3, SW14.4, SW14.5, SW14.6, SW15.1, SW15.2, SW15.3, SW15.4, SW15.5, SW15.6
VDDA4: J5.3, R57.2, R58.2, R59.2, R60.2, R61.2, R62.P$2, R70.2, SW18.1, SW18.2, SW18.3, SW18.4, SW18.5, SW18.6, SW19.1, SW19.2, SW19.3, SW19.4, SW19.5, SW19.6
VDDA5: J6.3, R71.2, R72.2, R73.2, R74.2, R75.2, R76.P$2, R84.2, SW22.1, SW22.2, SW22.3, SW22.4, SW22.5, SW22.6, SW23.1, SW23.2, SW23.3, SW23.4, SW23.5, SW23.6
VDDA6: J7.3, R85.2, R86.2, R87.2, R88.2, R89.2, R90.P$2, R98.2, SW26.1, SW26.2, SW26.3, SW26.4, SW26.5, SW26.6, SW27.1, SW27.2, SW27.3, SW27.4, SW27.5, SW27.6
VDDA7: J8.3, R99.2, R100.2, R101.2, R102.2, R103.2, R104.P$2, R112.2, SW30.1, SW30.2, SW30.3, SW30.4, SW30.5, SW30.6, SW31.1, SW31.2, SW31.3, SW31.4, SW31.5, SW31.6
VDDA8: J9.3, R113.2, R114.2, R115.2, R116.2, R117.2, R118.P$2, R126.2, SW34.1, SW34.2, SW34.3, SW34.4, SW34.5, SW34.6, SW35.1, SW35.2, SW35.3, SW35.4, SW35.5, SW35.6
VIN: J1.4, SW1.1, SW1.2, SW1.3, SW1.4, SW1.5, SW1.6
VIN1: J2.4, SW5.1, SW5.2, SW5.3, SW5.4, SW5.5, SW5.6
VIN2: J3.4, SW9.1, SW9.2, SW9.3, SW9.4, SW9.5, SW9.6
VIN3: J4.4, SW13.1, SW13.2, SW13.3, SW13.4, SW13.5, SW13.6
VIN4: J5.4, SW17.1, SW17.2, SW17.3, SW17.4, SW17.5, SW17.6
VIN5: J6.4, SW21.1, SW21.2, SW21.3, SW21.4, SW21.5, SW21.6
VIN6: J7.4, SW25.1, SW25.2, SW25.3, SW25.4, SW25.5, SW25.6
VIN7: J8.4, SW29.1, SW29.2, SW29.3, SW29.4, SW29.5, SW29.6
VIN8: J9.4, SW33.1, SW33.2, SW33.3, SW33.4, SW33.5, SW33.6
VOUT: C7.1, C8.1, C9.1, C10.1, C11.1, C12.-, C13.1, J1.2, SW4.1, SW4.2, SW4.3, SW4.4, SW4.5, SW4.6
VOUT1: C21.1, C22.1, C23.1, C24.1, C25.1, C26.-, C27.1, J2.2, SW8.1, SW8.2, SW8.3, SW8.4, SW8.5, SW8.6
VOUT2: C35.1, C36.1, C37.1, C38.1, C39.1, C40.-, C41.1, J3.2, SW12.1, SW12.2, SW12.3, SW12.4, SW12.5, SW12.6
VOUT3: C49.1, C50.1, C51.1, C52.1, C53.1, C54.-, C55.1, J4.2, SW16.1, SW16.2, SW16.3, SW16.4, SW16.5, SW16.6
VOUT4: C63.1, C64.1, C65.1, C66.1, C67.1, C68.-, C69.1, J5.2, SW20.1, SW20.2, SW20.3, SW20.4, SW20.5, SW20.6
VOUT5: C77.1, C78.1, C79.1, C80.1, C81.1, C82.-, C83.1, J6.2, SW24.1, SW24.2, SW24.3, SW24.4, SW24.5, SW24.6
VOUT6: C91.1, C92.1, C93.1, C94.1, C95.1, C96.-, C97.1, J7.2, SW28.1, SW28.2, SW28.3, SW28.4, SW28.5, SW28.6
VOUT7: C105.1, C106.1, C107.1, C108.1, C109.1, C110.-, C111.1, J8.2, SW32.1, SW32.2, SW32.3, SW32.4, SW32.5, SW32.6
VOUT8: C119.1, C120.1, C121.1, C122.1, C123.1, C124.-, C125.1, J9.2, SW36.1, SW36.2, SW36.3, SW36.4, SW36.5, SW36.6
